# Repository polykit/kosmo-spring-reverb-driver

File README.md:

# Kosmo Spring Reverb Driver

This repository contains KiCad schematics and PCB layout for a spring reverb driver in Kosmo modular synthesizer format. It is capable to drive reverbs with an impedance from 8 to 600 ohms. There is a short video at [https://www.youtube.com/watch?v=zHZOu3KcKBQ](https://www.youtube.com/watch?v=zHZOu3KcKBQ).

## Schematics

## Building

Just put everything in, all values are marked on the PCB. Start with the lowest profile. The board is also the front panel of the module so components stick out. It is also possible to solder most of the components on the back if wanted.

*You need a separate spring reverb tank for this module. Marked component values need to be changed depending on your reverbs impedance. The values written on the board are for 8 ohm impedance. I drive an Accutronics 4AB2A1C with it. You need to make sure that the input coil is not grounded to the tanks casing or it won't work.*

### Coil impedance

| Input Coil Impedance | R5, R13, R19 | R10     | R6, R7   | C2, C3 | 
|----------------------|--------------|---------|----------|--------|
| 8R                   | 100R         | 150R    | 4k7      | 100uF  |
| 150R                 | 470R         | 3k3     | 6k8      | 22uF   |
| 200R                 | 560R         | 3k9     | 6k8      | 22uF   |
| 250R                 | 680R         | 5k6     | 6k8      | 22uF   |
| 600R                 | 1k           | 12k     | 6k8      | 22uF   |

*I only tested values for 8 ohm impedance coils. You might need to fiddle around with listed values for good results.*

### BOM

|Designator|Quantity              |Designation                                      |
|----------|----------------------|-------------------------------------------------|
|C3,C2     |2                     |100u*                                            |
|R19,R13,R5|3                     |100*                                             |
|GAIN1     |1                     |100k trimpot 5mm                                 |
|R18       |1                     |1k                                               |
|REVERB_OUT1,REVERB_IN1|2                     |2 pin connector                                  |
|C9,C8     |2                     |22u                                              |
|C7,C6     |2                     |10u                                              |
|POWER1    |1                     |IDC 10 pin male connector                        |
|C11,C1    |2                     |100n                                             |
|C10       |1                     |1n                                               |
|C5        |1                     |22n                                              |
|OUT1,IN1  |2                     |Audio Jack 6,35mm                                |
|FEEDBACK_POT1|1                     |50k pot                                          |
|DRY_WET_POT1|1                     |10k pot                                          |
|U1        |1                     |TL074                                            |
|R17,R16,R3,R2,R1|5                     |100k                                             |
|R15,R14,R9,R8|4                     |10                                               |
|R12       |1                     |220                                              |
|R11       |1                     |2k2                                              |
|R10       |1                     |150*                                             |
|R7,R6     |2                     |4k7*                                             |
|R4        |1                     |10k                                              |
|Q2        |1                     |BC640                                            |
|Q1        |1                     |BC639                                            |
|D2,D1     |2                     |1N4148                                           |

## References

https://sound-au.com/articles/reverb.htm

https://kassu2000.blogspot.com/2015/10/spring-reverb.html

https://www.lookmumnocomputer.com/modular

https://github.com/telec16/kicad

https://github.com/holmesrichards/Kosmo_panel

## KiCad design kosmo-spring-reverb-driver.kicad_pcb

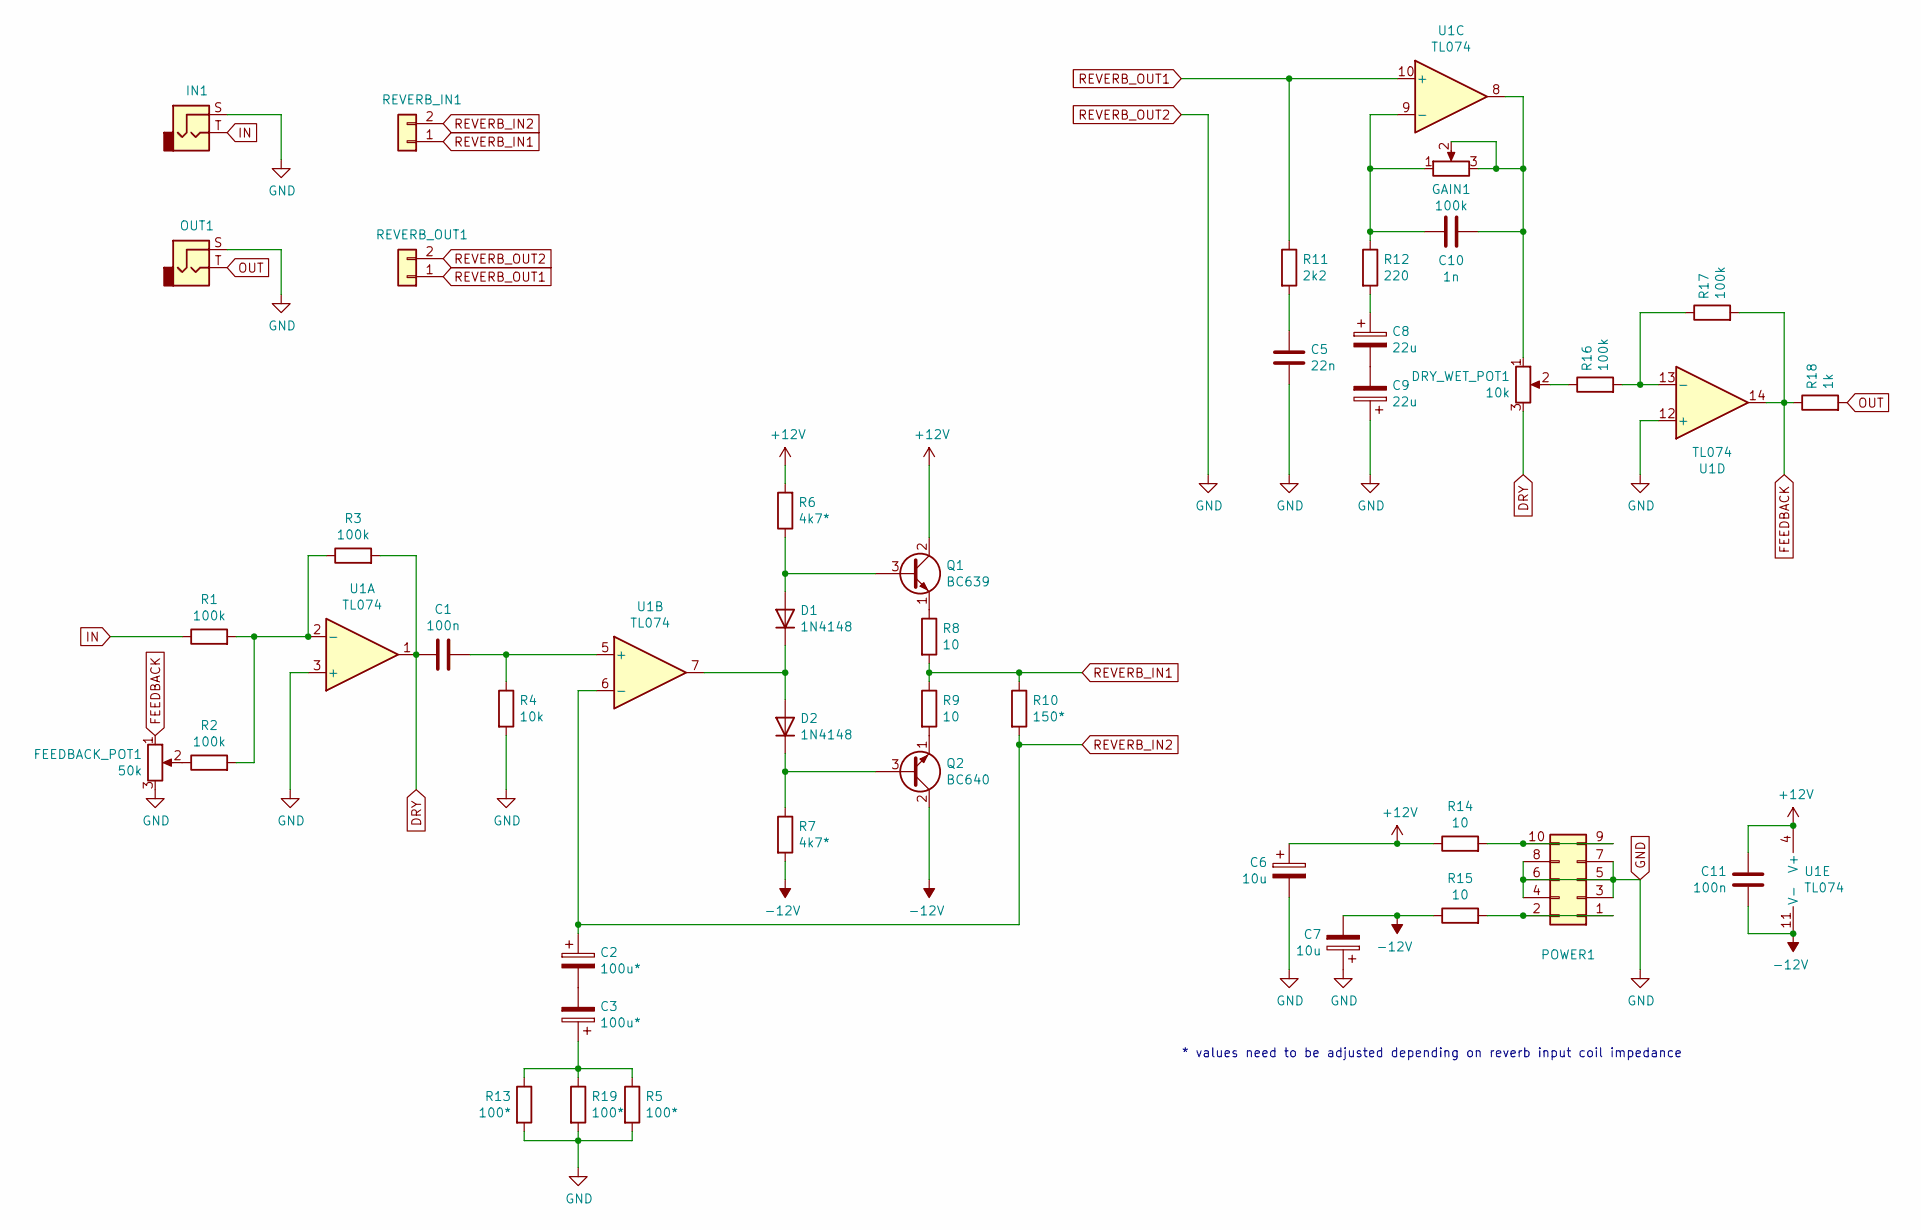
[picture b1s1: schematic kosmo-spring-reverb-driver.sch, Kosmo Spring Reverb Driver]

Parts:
C1, C11: 100n; C_Disc_D8.0mm_W2.5mm_P5.00mm
C2, C3: 100u*; CP_Radial_D6.3mm_P2.50mm
C5: 22n; C_Disc_D8.0mm_W2.5mm_P5.00mm
C6, C7: 10u; CP_Radial_D5.0mm_P2.50mm
C8, C9: 22u; CP_Radial_D5.0mm_P2.50mm
C10: 1n; C_Disc_D8.0mm_W2.5mm_P5.00mm
D1, D2: 1N4148; D_DO-35_SOD27_P7.62mm_Horizontal
DRY_WET_POT1: 10k; Potentiometer_Single_Vertical_Hole
FEEDBACK_POT1: 50k; Potentiometer_Single_Vertical_Hole
GAIN1: 100k; Potentiometer_ACP_CA9-H5_Horizontal
IN1: AudioJack2; Jack_Hole_Square
OUT1: AudioJack2; Jack_Hole_Square
POWER1: Conn_02x05_Odd_Even; IDC-Header_2x05_P2.54mm_Vertical
Q1: BC639; TO-92_Inline_Wide
Q2: BC640; TO-92_Inline_Wide
R1, R2, R3, R16, R17: 100k; R_Axial_DIN0207_L6.3mm_D2.5mm_P10.16mm_Horizontal
R4: 10k; R_Axial_DIN0207_L6.3mm_D2.5mm_P10.16mm_Horizontal
R5, R13, R19: 100*; R_Axial_DIN0207_L6.3mm_D2.5mm_P10.16mm_Horizontal
R6, R7: 4k7*; R_Axial_DIN0207_L6.3mm_D2.5mm_P10.16mm_Horizontal
R8, R9, R14, R15: 10; R_Axial_DIN0207_L6.3mm_D2.5mm_P10.16mm_Horizontal
R10: 150*; R_Axial_DIN0207_L6.3mm_D2.5mm_P10.16mm_Horizontal
R11: 2k2; R_Axial_DIN0207_L6.3mm_D2.5mm_P10.16mm_Horizontal
R12: 220; R_Axial_DIN0207_L6.3mm_D2.5mm_P10.16mm_Horizontal
R18: 1k; R_Axial_DIN0207_L6.3mm_D2.5mm_P10.16mm_Horizontal
REVERB_IN1: Conn_01x02; Molex_KK-254_AE-6410-02A_1x02_P2.54mm_Vertical
REVERB_OUT1: Conn_01x02; Molex_KK-254_AE-6410-02A_1x02_P2.54mm_Vertical
U1: TL074; DIP-14_W7.62mm_Socket_LongPads

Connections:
+12V: C6.1, C11.2, Q1.2 (C), R6.2, R14.1, U1.4 (V+)
-12V: C7.2, C11.1, Q2.2 (C), R7.2, R15.1, U1.11 (V-)
DRY: C1.1, DRY_WET_POT1.3, R3.2, U1.1
FEEDBACK: FEEDBACK_POT1.1, R17.2, R18.1, U1.14
GND: C5.1, C6.2, C7.1, C9.1, FEEDBACK_POT1.3, IN1.S, OUT1.S, POWER1.3, POWER1.4, POWER1.5, POWER1.6, POWER1.7, POWER1.8, R4.2, R5.2, R13.2, R19.2, REVERB_OUT1.2, U1.3 (+), U1.12 (+)
IN: IN1.T, R1.1
unnamed: C1.2, R4.1, U1.5 (+)
unnamed: C2.2, C3.2
unnamed: C3.1, R5.1, R13.1, R19.1
unnamed: C5.2, R11.2
unnamed: C8.1, R12.2
unnamed: C8.2, C9.2
unnamed: C10.1, DRY_WET_POT1.1, GAIN1.2, GAIN1.3, U1.8
unnamed: C10.2, GAIN1.1, R12.1, U1.9 (-)
unnamed: D1.1 (K), D2.2 (A), U1.7
unnamed: D1.2 (A), Q1.3 (B), R6.1
unnamed: D2.1 (K), Q2.3 (B), R7.1
unnamed: DRY_WET_POT1.2, R16.1
unnamed: FEEDBACK_POT1.2, R2.1
unnamed: POWER1.1, POWER1.2, R15.2
unnamed: POWER1.9, POWER1.10, R14.2
unnamed: Q1.1 (E), R8.1
unnamed: Q2.1 (E), R9.2
unnamed: R1.2, R2.2, R3.1, U1.2 (-)
unnamed: R16.2, R17.1, U1.13 (-)
OUT: OUT1.T, R18.2
REVERB_IN1: R8.2, R9.1, R10.1, REVERB_IN1.1
REVERB_IN2: C2.1, R10.2, REVERB_IN1.2, U1.6 (-)
REVERB_OUT1: R11.1, REVERB_OUT1.1, U1.10 (+)

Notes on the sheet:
* values need to be adjusted depending on reverb input coil impedance

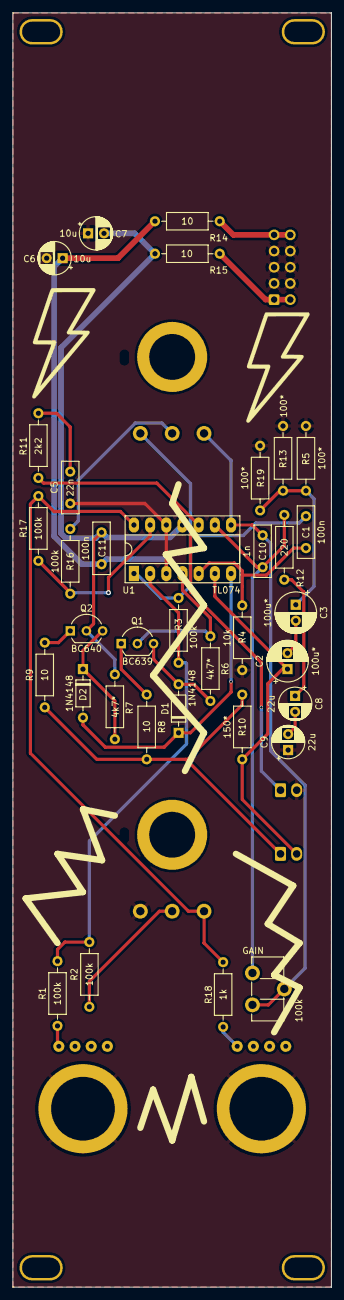
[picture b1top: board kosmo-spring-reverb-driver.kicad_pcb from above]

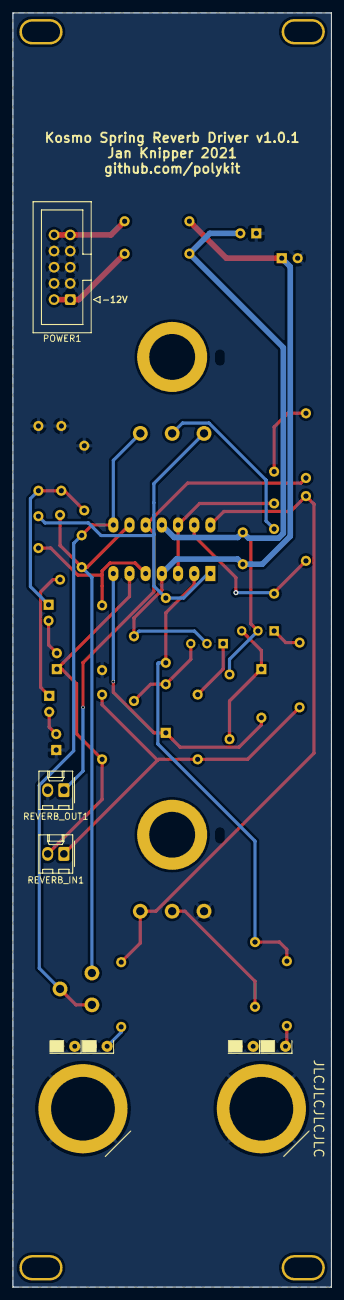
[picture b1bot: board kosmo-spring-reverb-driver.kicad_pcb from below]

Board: 2 copper layers, 50.0 x 200.0 mm, 42 parts (3 on the bottom side), 29 nets.

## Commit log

2021-03-06 Initial import
2021-03-06 Added documentation
2021-03-06 Added footprint libraries
2021-03-07 Fix pot hole size, cap position
2021-10-08 Add image for modulargrid
2021-10-08 Add small multigrid image
2021-10-08 Changes readme
2024-01-17 Redo gerber files
